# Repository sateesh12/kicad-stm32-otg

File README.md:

# kicad-stm32-otg
KiCAD based hardware design for an STM32 with USB OTG.

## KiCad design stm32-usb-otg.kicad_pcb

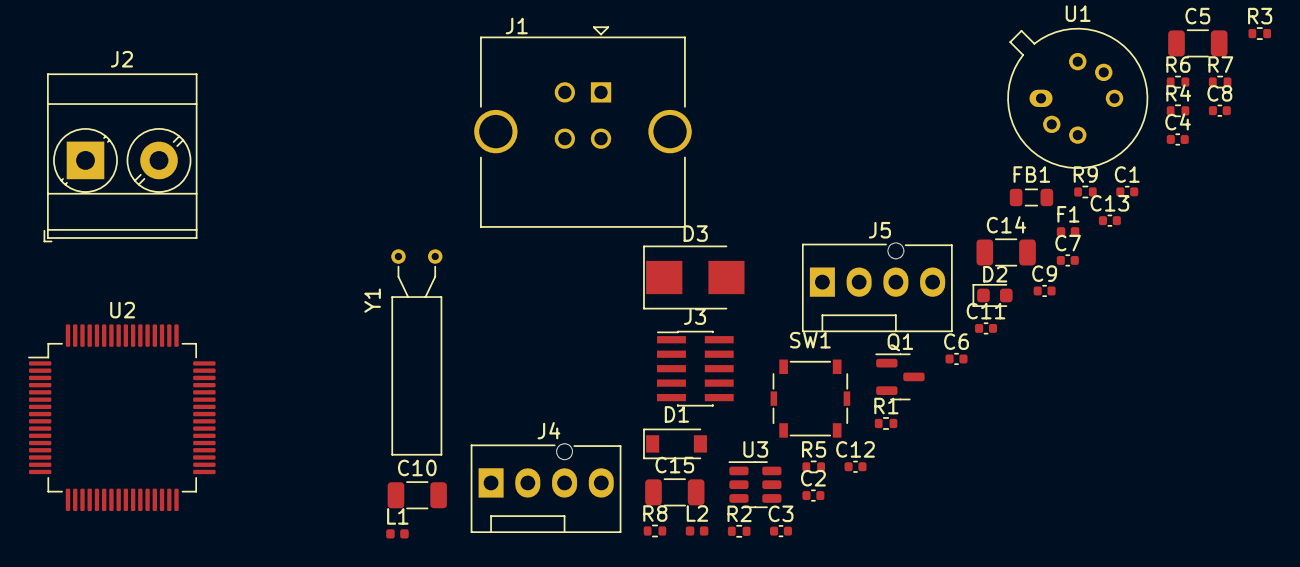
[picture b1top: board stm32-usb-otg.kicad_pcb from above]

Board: 4 copper layers, 42 parts (0 on the bottom side), 34 nets, no tracks yet.

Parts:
C1: 4u7; C_0402_1005Metric
C2, C4, C6, C8, C9: 100n; C_0402_1005Metric
C3, C7: 10p; C_0402_1005Metric
C5: 10nF; C_1206_3216Metric
C10: 2u2; C_1206_3216Metric
C11: 1u; C_0402_1005Metric
C12: 2u2; C_0402_1005Metric
C13: 1n; C_0402_1005Metric
C14: 10n; C_1206_3216Metric
C15: 22u; C_1206_3216Metric
D1: D_Schottky; D_SOD-123
D2: Blue; LED_0603_1608Metric
D3: B230; D_SMB
F1: 250mA; Fuse_0402_1005Metric
FB1: FerriteBead_Small; L_0805_2012Metric
J1: USB_B_Micro; USB_B_Amphenol_MUSB-D511_Vertical_Rugged
J2: Screw_Terminal_01x02; TerminalBlock_Phoenix_MKDS-3-2-5.08_1x02_P5.08mm_Horizontal
J3: SWD; PinHeader_2x05_P1.00mm_Vertical_SMD
J4: I2C Connector; FanPinHeader_1x04_P2.54mm_Vertical
J5: Conn_01x04; FanPinHeader_1x04_P2.54mm_Vertical
L1: 39n; L_0402_1005Metric
L2: 4.7u; L_0402_1005Metric
Q1: AO3401A; SOT-23
R1: 10k; R_0402_1005Metric
R2: 47; R_0402_1005Metric
R3: 100k; R_0402_1005Metric
R4: 68k; R_0402_1005Metric
R5, R6: 2k2; R_0402_1005Metric
R7: 1k5; R_0402_1005Metric
R8: 49.9k; R_0402_1005Metric
R9: 16.2k; R_0402_1005Metric
SW1: SW_SPDT; SW_SPST_Panasonic_EVQPL_3PL_5PL_PT_A08
U1: MP2359; TO-5-6
U2: STM32F405RGT6; LQFP-64_10x10mm_P0.5mm
U3: USBLC6-2SC6; SOT-23-6
Y1: 16MHz; Crystal_AT310_D3.0mm_L10.0mm_Horizontal

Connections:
+3.3VA: C15.1, L1.1, L2.2, R8.1, U2.13 (VDDA)
+3.3VP: C1.1, C2.1, C4.1, C6.1, C8.1, C9.1, J3.1, R5.1, R6.1, U2.1 (VBAT), U2.19 (VDD), U2.32 (VDD), U2.48 (VDD), U2.64 (VDD)
+3V3: J4.1, J5.1, SW1.1 (A)
+5V: D1.2 (A), J1.1 (VBUS), U3.5 (VBUS)
+12P: F1.1, J2.1
BOOT0: R1.1, U2.60 (BOOT0)
BUCK_BST: C14.1, U1.1 (BST)
BUCK_EN: R3.2, R4.1, U1.4 (EN)
BUCK_FB: R8.2, R9.1, U1.3 (FB)
BUCK_IN: C5.1, FB1.2, R3.1, U1.5 (IN)
BUCK_SW: C14.2, D3.1 (K), L2.1, U1.6 (SW)
GND: C1.2, C2.2, C3.2, C4.2, C5.2, C6.2, C7.2, C8.2, C9.2, C10.2, C11.2, C12.2, C13.2, C15.2, D3.2 (A), J1.5 (GND), J2.2, J3.3, J3.5, J3.9, J4.4, J5.4, Q1.1 (G), R4.2, R7.2, R9.2, U1.2 (GND), U2.12 (VSSA), U2.18 (VSS), U2.63 (VSS), U3.2 (GND), Y1.2
HSE_IN: C3.1, U2.5 (PH0), Y1.1
HSE_OUT: R2.1, U2.6 (PH1)
I2C1_SCLK: J4.2, R5.2, U2.58 (PB6)
I2C1_SDA: J4.3, R6.2, U2.59 (PB7)
LED_STATUS: D2.2 (A), U2.16 (PA2)
NRST: J3.10, U2.7 (NRST)
unnamed: C7.1, R2.2
unnamed: C10.1, U2.31 (VCAP_1)
unnamed: C11.1, C13.1, L1.2
unnamed: C12.1, U2.47 (VCAP_2)
unnamed: D1.1 (K), FB1.1, Q1.2 (S)
unnamed: D2.1 (K), R7.1
unnamed: F1.2, Q1.3 (D)
unnamed: R1.2, SW1.2 (B)
SWD_SCLK: J3.4, U2.49 (PA14)
SWD_SWDIO: J3.2, U2.46 (PA13)
USART3_RX: J5.3, U2.52 (PC11)
USART3_TX: J5.2, U2.51 (PC10)
USB_CONN_D_+: J1.3 (D+), U3.3 (I/O2)
USB_CONN_D_-: J1.2 (D-), U3.1 (I/O1)
USB_D+: U2.45 (PA12), U3.4 (I/O2)
USB_D-: U2.44 (PA11), U3.6 (I/O1)

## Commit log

2022-02-18 Added first version of the KiCAD files Added a .gitignore file as well
2022-02-18 Added more ignore directories based on KiCAD
2022-02-18 Moved the schematic items to bottom left hand corner.
2022-02-18 Connected LED as a status indicator to the schematic.
2022-02-18 Added a custom schematic symbol for the buck regulator.
2022-02-18 Added parts of the buck convertor.
2022-02-18 Completd the ckt for the Buck regulator.
2022-02-18 Added power connector.
2022-02-18 Added SWD connector.
2022-02-19 Add UART, I2C connectors.
2022-02-19 Added USB TVS protection.
2022-02-19 Resolving a few ERC errors with power flag based power.
2022-02-19 Solving a few ERC errors.
2022-02-19 Solved all Warnings !
2022-02-19 Solved all errors by adding "Power flag" connectors.
2022-02-19 Generated a net-list.
2022-02-19 An simple resistive divider in LTSpice.
